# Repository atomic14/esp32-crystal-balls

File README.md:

# Look At My Shiny Crystal Balls!

This PCB is now supporting two of my projects: [Crystal Balls](https://www.youtube.com/watch?v=1-Rm0mgg2RI) and my [Flame Lamp](https://youtu.be/qe_sFo2qRoI).

I got some of these [crystal balls](https://s.click.aliexpress.com/e/_DDdvNqJ) from AliExpress for Christmas.

The base is pretty simple, it's just some LEDs and resistors connected to the 5v USB power supply.

So, I decided to make something a bit more sophisticated.

It's based around an ESP32-S3-Mini which means it can run the popular WLED firmware.

It's a pretty compact PCB.

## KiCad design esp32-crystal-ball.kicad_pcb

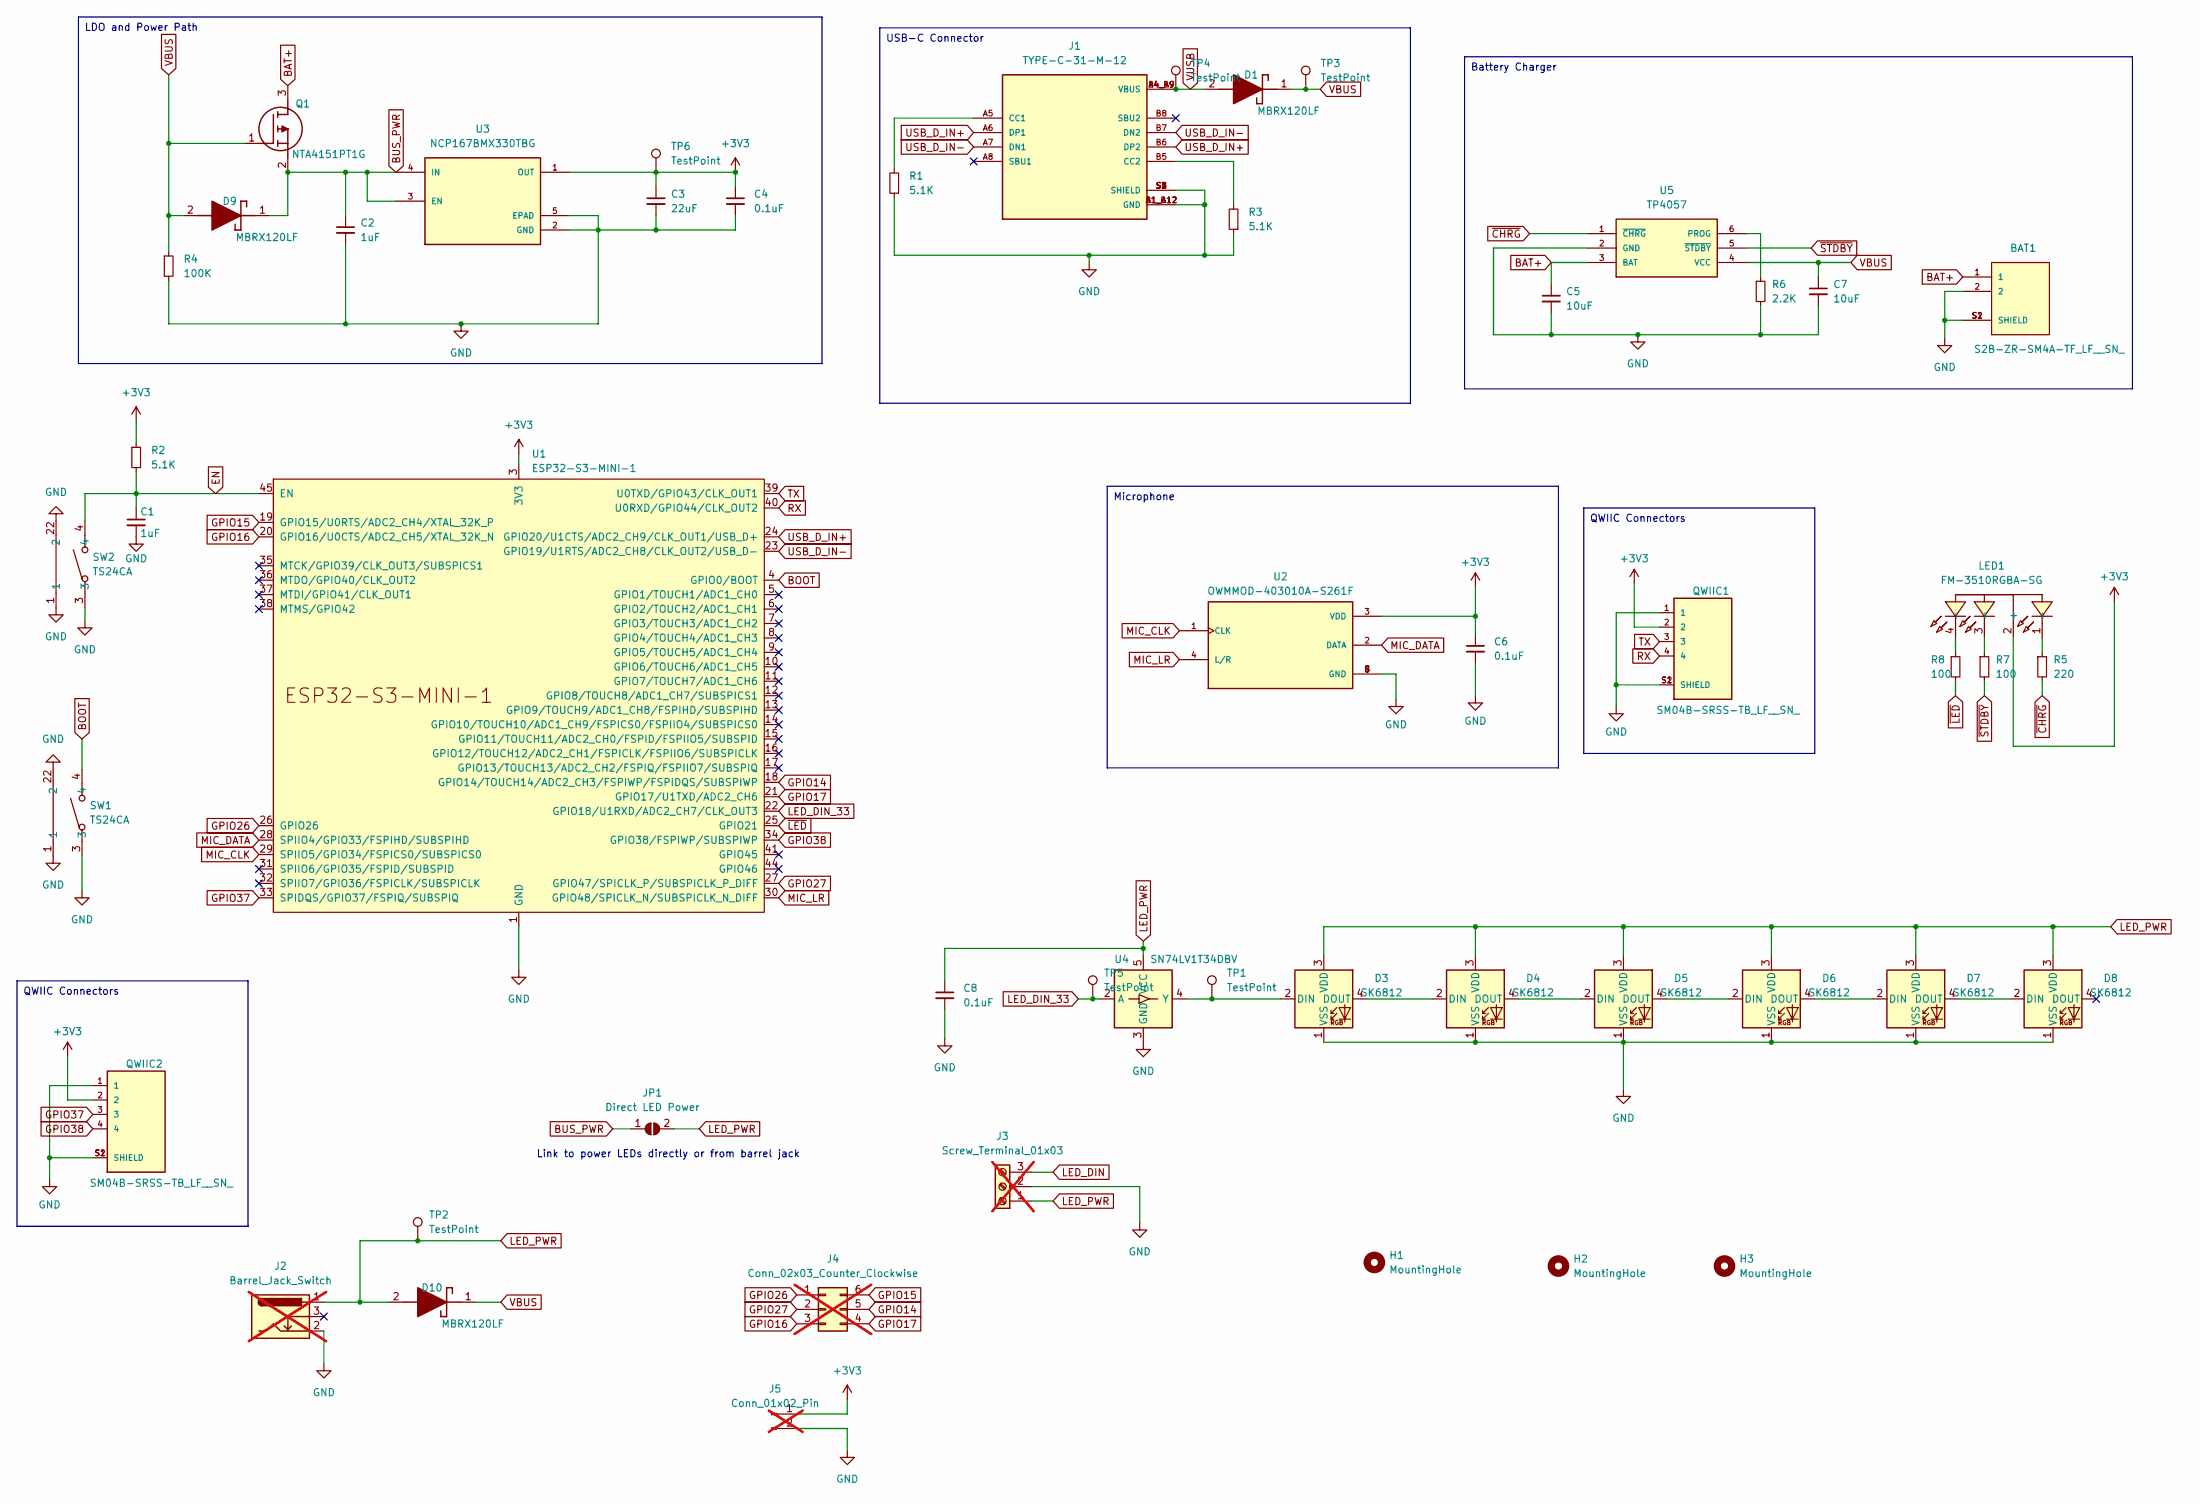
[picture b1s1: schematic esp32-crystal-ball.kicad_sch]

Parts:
BAT1: S2B-ZR-SM4A-TF_LF__SN_; JST_S2B-ZR-SM4A-TF_LF__SN_; PARTREV N/A
C1: 1uF; C_0603_1608Metric
C2: 1uF; C_0603_1608Metric; Mfg Part # test
C3: 22uF; C_0603_1608Metric
C4, C6, C8: 0.1uF; C_0603_1608Metric
C5, C7: 10uF; C_0603_1608Metric
D1, D9, D10: MBRX120LF; D_SOD-123
D3, D4, D5, D6, D7, D8: SK6812; LED_SK6812_PLCC4_5.0x5.0mm_P3.2mm
H1, H2, H3: MountingHole; MountingHole_3.2mm_M3
J1: TYPE-C-31-M-12; HRO_TYPE-C-31-M-12; PARTREV 2020.12.08
J2: Barrel_Jack_Switch; BarrelJack_Horizontal; not fitted
J3: Screw_Terminal_01x03; PhoenixContact_MCV_1,5_3-G-3.5_1x03_P3.50mm_Vertical; MPN MKDS 1/ 3-3,5; not fitted
J4: Conn_02x03_Counter_Clockwise; PinHeader_2x03_P2.54mm_Vertical_SMD; not fitted
J5: Conn_01x02_Pin; PinHeader_1x02_P2.54mm_Vertical_SMD_Pin1Left; not fitted
JP1: Direct LED Power; SolderJumper-2_P1.3mm_Open_RoundedPad1.0x1.5mm
LED1: FM-3510RGBA-SG; LED-SMD_FM-3510RGBA-SG; LCSC Part C727903
Q1: NTA4151PT1G; SOT50P160X90-3N; Mouser Part Number 863-NTA4151PT1G
QWIIC1, QWIIC2: SM04B-SRSS-TB_LF__SN_; JST_SM04B-SRSS-TB_LF__SN_
R1, R2, R3: 5.1K; R_0603_1608Metric
R4: 100K; R_0603_1608Metric
R5: 220; R_0603_1608Metric
R6: 2.2K; R_0603_1608Metric
R7, R8: 100; R_0603_1608Metric
SW1, SW2: TS24CA; SW-SMD_TS24CA; LCSC Part C393942
TP1, TP2, TP3, TP4, TP5, TP6: TestPoint; TestPoint_Pad_D2.5mm
U1: ESP32-S3-MINI-1
U2: OWMMOD-403010A-S261F; MIC_OWMMOD-403010A-S261F; PARTREV 00; DigiKey_Part_Number 3949-OWMMOD-403010A-S261F-ND
U3: NCP167BMX330TBG; VREG_NCP167BMX330TBG; PARTREV 5
U4: SN74LV1T34DBV; SOT-23-5
U5: TP4057; SOT-23-6

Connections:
+3V3: C3.1, C4.1, C6.1, J5.1, LED1.2 (+), QWIIC1.2, QWIIC2.2, R2.1, TP6.1, U1.3 (3V3), U2.3 (VDD), U3.1 (OUT)
BAT+: BAT1.1, C5.1, Q1.3 (D), U5.3 (BAT)
BOOT: SW1.4, U1.4 (GPIO0/BOOT); also elsewhere on the board
BUS_PWR: C2.1, D9.1 (K), JP1.1 (A), Q1.2 (S), U3.3 (EN), U3.4 (IN)
EN: C1.1, R2.2, U1.45 (EN); also elsewhere on the board
GND: BAT1.2, BAT1.S1 (SHIELD), BAT1.S2 (SHIELD), C1.2, C2.2, C3.2, C4.2, C5.2, C6.2, C7.2, C8.2, D3.1 (VSS), D4.1 (VSS), D5.1 (VSS), D6.1 (VSS), D7.1 (VSS), D8.1 (VSS), J1.A1_B12 (GND), J1.B1_A12 (GND), J1.S1 (SHIELD), J1.S2 (SHIELD), J1.S3 (SHIELD), J1.S4 (SHIELD), J2.2, J3.2, J5.2, QWIIC1.1, QWIIC1.S1 (SHIELD), QWIIC1.S2 (SHIELD), QWIIC2.1, QWIIC2.S1 (SHIELD), QWIIC2.S2 (SHIELD), R1.1, R3.1, R4.2, R6.2, U1.1 (GND), U1.2 (GND), U1.42 (GND), U1.43 (GND), U1.46 (GND), U1.47 (GND), U1.48 (GND), U1.49 (GND), U1.50 (GND), U1.51 (GND), U1.52 (GND), U1.53 (GND), U1.54 (GND), U1.55 (GND), U1.56 (GND), U1.57 (GND), U1.58 (GND), U1.59 (GND), U1.60 (GND), U1.61 (GND), U1.62 (GND), U1.63 (GND), U1.64 (GND), U1.65 (GND), U2.5 (GND), U2.6 (GND), U2.7 (GND), U2.8 (GND), U3.2 (GND), U3.5 (EPAD), U4.3 (GND), U5.2 (GND); also elsewhere on the board
GPIO14: J4.5, U1.18 (GPIO14/TOUCH14/ADC2_CH3/FSPIWP/FSPIDQS/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)
GPIO15: J4.6, U1.19 (GPIO15/U0RTS/ADC2_CH4/XTAL_32K_P)
GPIO16: J4.3, U1.20 (GPIO16/U0CTS/ADC2_CH5/XTAL_32K_N)
GPIO17: J4.4, U1.21 (GPIO17/U1TXD/ADC2_CH6)
GPIO26: J4.1, U1.26 (GPIO26)
GPIO27: J4.2, U1.27 (GPIO47/SPICLK_P/SUBSPICLK_P_DIFF)
GPIO37: QWIIC2.3, U1.33 (SPIDQS/GPIO37/FSPIQ/SUBSPIQ)
GPIO38: QWIIC2.4, U1.34 (GPIO38/FSPIWP/SUBSPIWP)
LED_DIN_33: TP5.1, U1.22 (GPIO18/U1RXD/ADC2_CH7/CLK_OUT3), U4.2 (A)
LED_PWR: C8.1, D3.3 (VDD), D4.3 (VDD), D5.3 (VDD), D6.3 (VDD), D7.3 (VDD), D8.3 (VDD), D10.2 (A), J2.1, J3.1, JP1.2 (B), TP2.1, U4.5 (VCC)
MIC_CLK: U1.29 (SPIIO5/GPIO34/FSPICS0/SUBSPICS0), U2.1 (CLK)
MIC_DATA: U1.28 (SPIIO4/GPIO33/FSPIHD/SUBSPIHD), U2.2 (DATA)
MIC_LR: U1.30 (GPIO48/SPICLK_N/SUBSPICLK_N_DIFF), U2.4 (L/R)
unnamed: D3.4 (DOUT), D4.2 (DIN)
unnamed: D4.4 (DOUT), D5.2 (DIN)
unnamed: D5.4 (DOUT), D6.2 (DIN)
unnamed: D6.4 (DOUT), D7.2 (DIN)
unnamed: D7.4 (DOUT), D8.2 (DIN)
unnamed: J1.A5 (CC1), R1.2
unnamed: J1.B5 (CC2), R3.2
unnamed: LED1.1 (-), R5.1
unnamed: LED1.3 (-), R7.1
unnamed: LED1.4 (-), R8.1
unnamed: R6.1, U5.6 (PROG)
RX: QWIIC1.4, U1.40 (U0RXD/GPIO44/CLK_OUT2)
TX: QWIIC1.3, U1.39 (U0TXD/GPIO43/CLK_OUT1)
USB_D_IN+: J1.A6 (DP1), J1.B6 (DP2), U1.24 (GPIO20/U1CTS/ADC2_CH9/CLK_OUT1/USB_D+)
USB_D_IN-: J1.A7 (DN1), J1.B7 (DN2), U1.23 (GPIO19/U1RTS/ADC2_CH8/CLK_OUT2/USB_D-)
VBUS: C7.1, D1.1 (K), D9.2 (A), D10.1 (K), Q1.1 (G), R4.1, TP3.1, U5.4 (VCC)
VUSB: D1.2 (A), J1.A4_B9 (VBUS), J1.B4_A9 (VBUS), TP4.1
~CHRG: R5.2, U5.1 (~CHRG)
~LED: R8.2, U1.25 (GPIO21)
~STDBY: R7.2, U5.5 (~STDBY)

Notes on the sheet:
QWIIC Connectors
LDO and Power Path
USB-C Connector
Microphone
Battery Charger
Link to power LEDs directly or from barrel jack

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
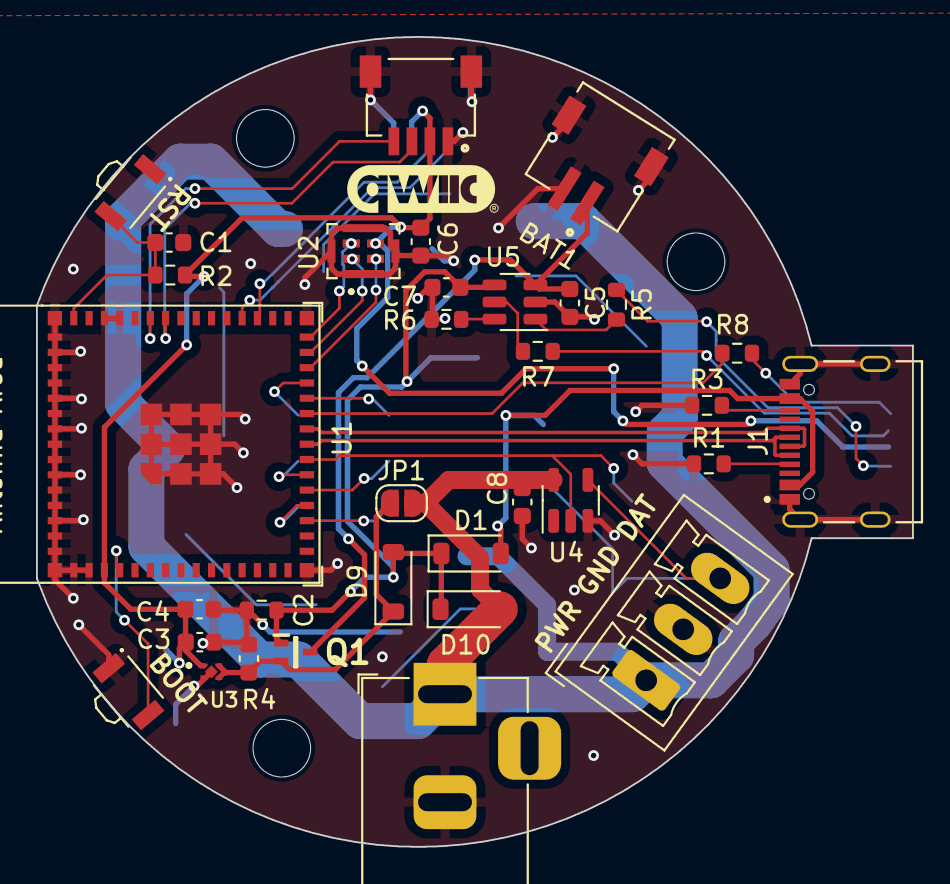
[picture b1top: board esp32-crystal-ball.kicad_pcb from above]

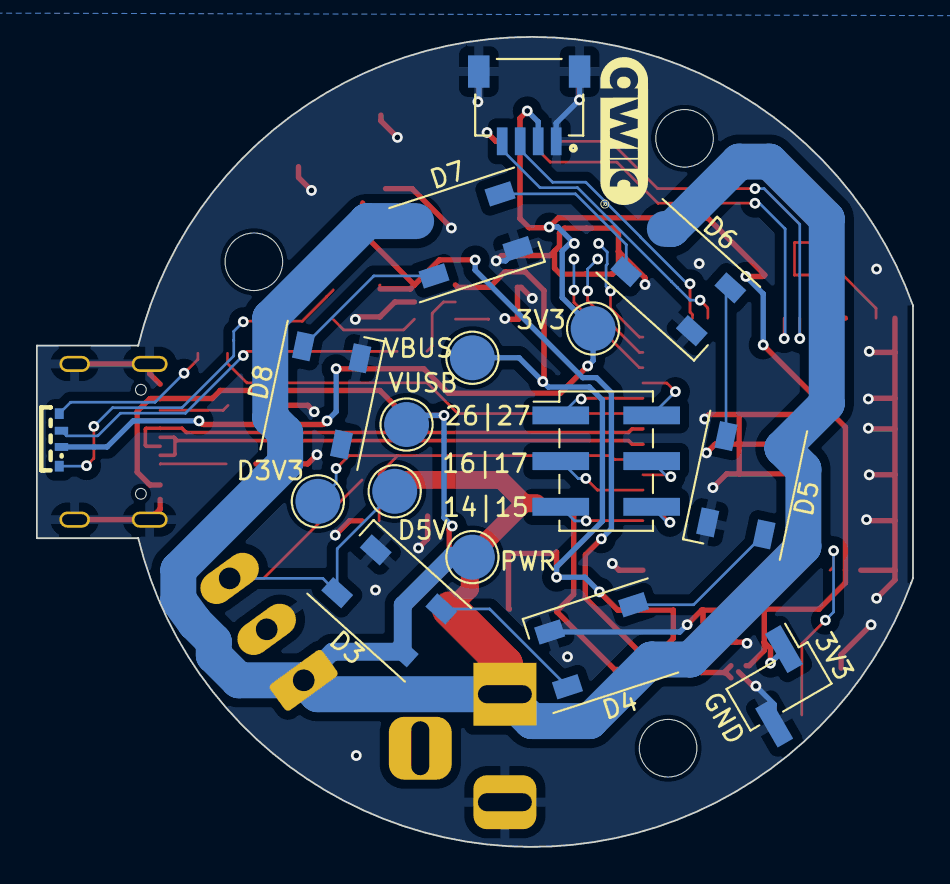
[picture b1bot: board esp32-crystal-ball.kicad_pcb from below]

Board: 2 copper layers, 48.7 x 45.0 mm, 52 parts (16 on the bottom side), 40 nets.

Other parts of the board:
BOOT1: B3U-3000P; SW_B3U-3000P
EN1: B3U-3000P; SW_B3U-3000P

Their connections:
BOOT: BOOT1.2; also elsewhere on the board
EN: EN1.2; also elsewhere on the board
GND: BOOT1.1, EN1.1; also elsewhere on the board

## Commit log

2024-04-19 Adds images and README file.
2024-05-12 Fix silk screen
2024-10-04 Fixes voltage regulator footprint
